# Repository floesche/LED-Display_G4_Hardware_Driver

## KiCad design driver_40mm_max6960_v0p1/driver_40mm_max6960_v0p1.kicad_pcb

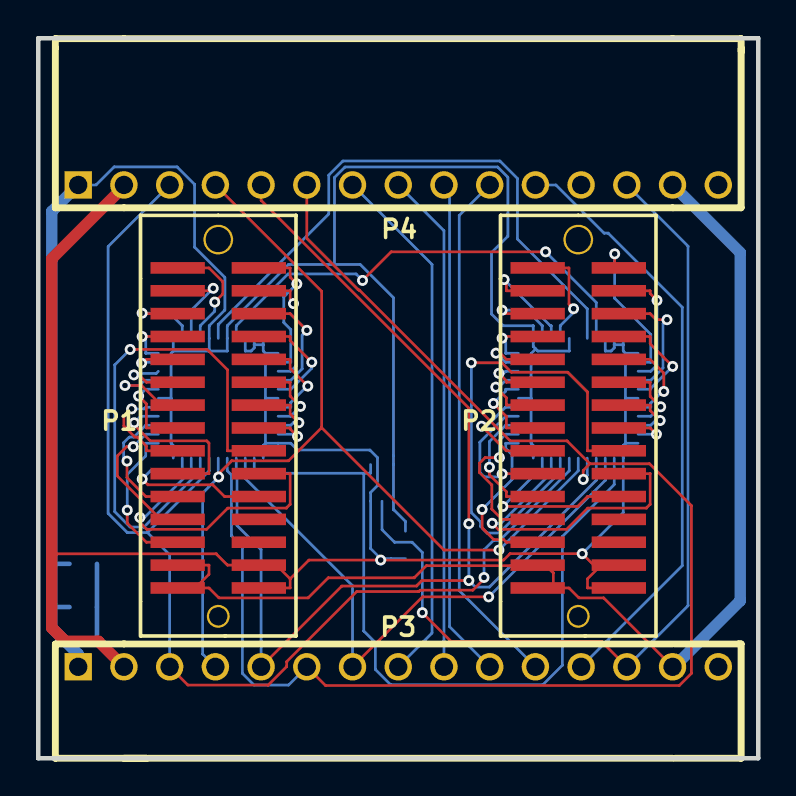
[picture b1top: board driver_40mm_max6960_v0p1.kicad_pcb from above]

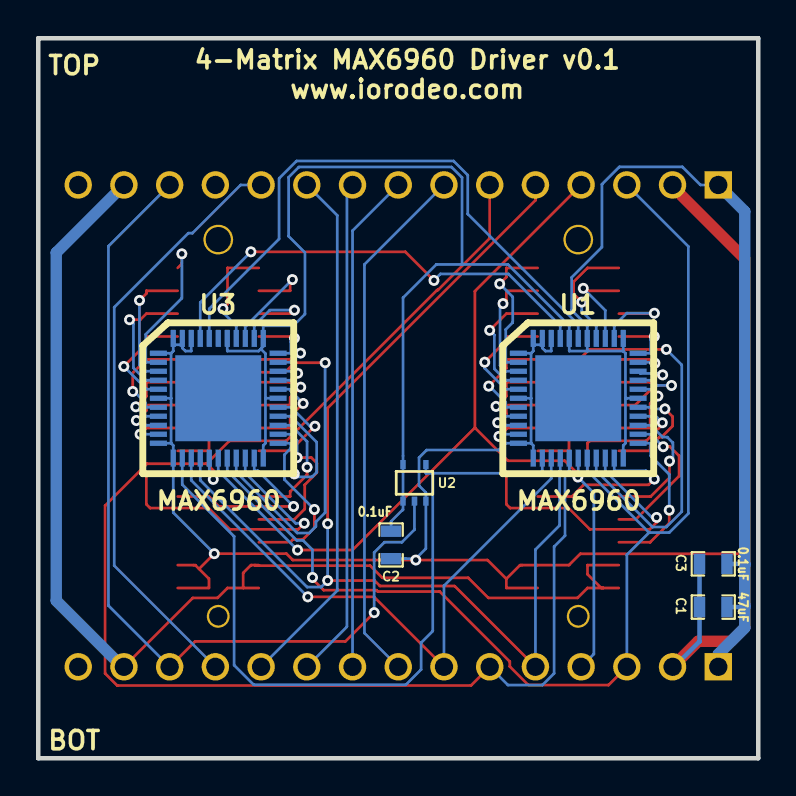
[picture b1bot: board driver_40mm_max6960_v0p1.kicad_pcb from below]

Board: 2 copper layers, 40.0 x 40.0 mm, 10 parts (6 on the bottom side), 65 nets.

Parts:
C1: 47uF; SM0603_Capa
C2, C3: 0.1uF; SM0603_Capa
P1, P2: CONN15X2; SMD_PIN_ARRAY_M_0P5IN_15X2
P3: CONN15; HEADER_BOT
P4: CONN15; HEADER_TOP
U1, U3: MAX6960; T4477-3
U2: 74AHC1G126; SOT353

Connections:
/ADDCLK: U1.41, U3.41
/ADDOUT_A: U1.39, U3.40
/CLK: P3.4, P4.4, U1.17, U3.17
/COL_A1: P1.18, U1.19
/COL_A2: P1.20, U1.20
/COL_A3: P1.22, U1.21
/COL_A4: P1.25, U1.23
/COL_A5: P1.23, U1.24
/COL_A6: P1.21, U1.25
/COL_A7: P1.19, U1.26
/COL_A8: P1.17, U1.27
/COL_A9: P1.15, U1.29
/COL_A10: P1.13, U1.30
/COL_A11: P1.11, U1.31
/COL_A12: P1.9, U1.32
/COL_A13: P1.7, U1.33
/COL_A14: P1.5, U1.35
/COL_A15: P1.3, U1.36
/COL_A16: P1.1, U1.37
/COL_B1: P2.18, U3.19
/COL_B2: P2.20, U3.20
/COL_B3: P2.22, U3.21
/COL_B4: P2.25, U3.23
/COL_B5: P2.23, U3.24
/COL_B6: P2.21, U3.25
/COL_B7: P2.19, U3.26
/COL_B8: P2.17, U3.27
/COL_B9: P2.15, U3.29
/COL_B10: P2.13, U3.30
/COL_B11: P2.11, U3.31
/COL_B12: P2.9, U3.32
/COL_B13: P2.7, U3.33
/COL_B14: P2.5, U3.35
/COL_B15: P2.3, U3.36
/COL_B16: P2.1, U3.37
/CS1: P3.7, U1.14, U3.14
/CS2: P3.8, P4.7
/CS3: P3.9, P4.8
/CS4: P3.10, P4.9
/CS5: P3.11, P4.10
/CS6: P3.12, P4.11
/MISO: P3.6, P4.6, U1.16, U3.16
/MOSI: P3.5, P4.5, U1.15, U3.15
/OSC: P3.13, P4.13, U2.2
/OSC_BUF: U1.13, U2.4, U3.13
/ROW_A1: P1.2, U1.2
/ROW_A2: P1.4, U1.3
/ROW_A3: P1.6, U1.4
/ROW_A4: P1.8, U1.5
/ROW_A5: P1.10, U1.7
/ROW_A6: P1.12, U1.8
/ROW_A7: P1.14, U1.9
/ROW_A8: P1.16, U1.10
/ROW_B1: P2.2, U3.2
/ROW_B2: P2.4, U3.3
/ROW_B3: P2.6, U3.4
/ROW_B4: P2.8, U3.5
/ROW_B5: P2.10, U3.7
/ROW_B6: P2.12, U3.8
/ROW_B7: P2.14, U3.9
/ROW_B8: P2.16, U3.10
/RST: P3.3, P4.3, U1.18, U3.18
/V+: C1.1, C2.1, C3.1, P3.1, P4.1, U1.22, U1.28, U1.34, U1.38, U1.40, U2.1, U2.5, U3.22, U3.28, U3.34, U3.38
/VAUX: P1.27, P1.29, P2.27, P2.29, P3.14, P4.14
GND: C1.2, C2.2, C3.2, P1.28, P1.30, P2.28, P2.30, P3.2, P4.2, U1.1, U1.6, U1.11, U1.12, U1.42, U1.43, U1.44, U2.3, U3.1, U3.6, U3.11, U3.12, U3.42, U3.43, U3.44
